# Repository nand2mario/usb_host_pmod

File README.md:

# USB Host PMOD

Design sources for a **dual-socket USB host PMOD** module, intended for interfacing USB devices on FPGA boards using [usb_hid_host](https://github.com/nand2mario/usb_hid_host). 

Included are [KiCAD sources](kicad/) and [production files](production/)(Gerber/BOM/PNP).

The easiest way to obtain the module is by following the [guide to directly order from JLCPCB](doc/guide.md).

This little design is done by [@regymm0](https://twitter.com/regymm0), [@ico_TC](https://twitter.com/ico_TC) and [@nand2mario](https://twitter.com/nand2mario).

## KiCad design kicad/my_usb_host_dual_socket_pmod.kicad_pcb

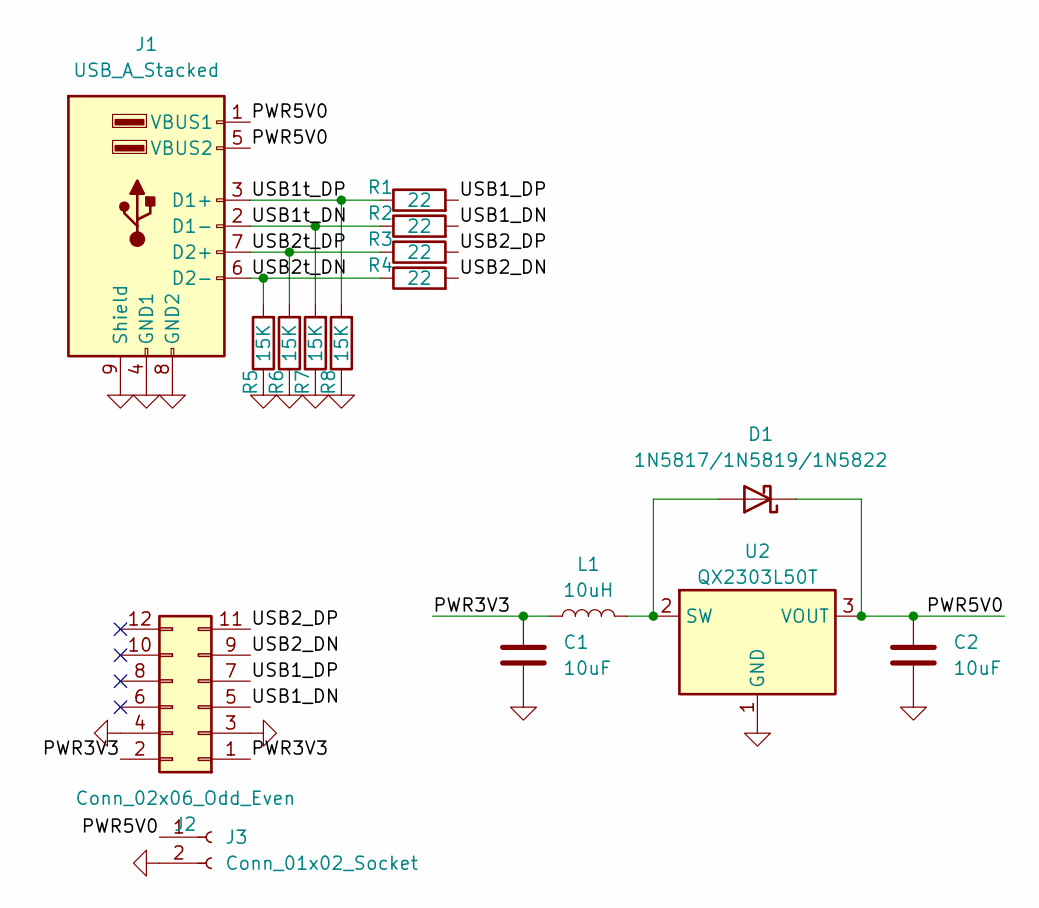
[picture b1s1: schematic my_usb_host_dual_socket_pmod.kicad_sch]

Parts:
C1, C2: 10uF; C_0402_1005Metric
D1: 1N5817/1N5819/1N5822; D_0402_1005Metric
J1: USB_A_Stacked; USB_A_Wuerth_61400826021_Horizontal_Stacked
J2: Conn_02x06_Odd_Even; PinHeader_2x06_P2.54mm_Horizontal
J3: Conn_01x02_Socket; PinSocket_1x02_P2.54mm_Vertical
L1: 10uH; L_0603_1608Metric
R1, R2, R3, R4: 22; R_0402_1005Metric
R5, R6, R7, R8: 15K; R_0402_1005Metric
U2: QX2303L50T; SOT-23

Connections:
/PWR3V3: C1.1, J2.1, J2.2, L1.1
/PWR5V0: C2.1, D1.1 (K), J1.1 (VBUS1), J1.5 (VBUS2), J3.1, U2.3 (VOUT)
/USB1_DN: J2.5, R2.2
/USB1_DP: J2.7, R1.2
/USB1t_DN: J1.2 (D1-), R2.1, R7.2
/USB1t_DP: J1.3 (D1+), R1.1, R8.2
/USB2_DN: J2.9, R4.2
/USB2_DP: J2.11, R3.2
/USB2t_DN: J1.6 (D2-), R4.1, R5.2
/USB2t_DP: J1.7 (D2+), R3.1, R6.2
GND: C1.2, C2.2, J1.4 (GND1), J1.8 (GND2), J1.9 (Shield), J2.3, J2.4, J3.2, R5.1, R6.1, R7.1, R8.1, U2.1 (GND)
unnamed: D1.2 (A), L1.2, U2.2 (SW)

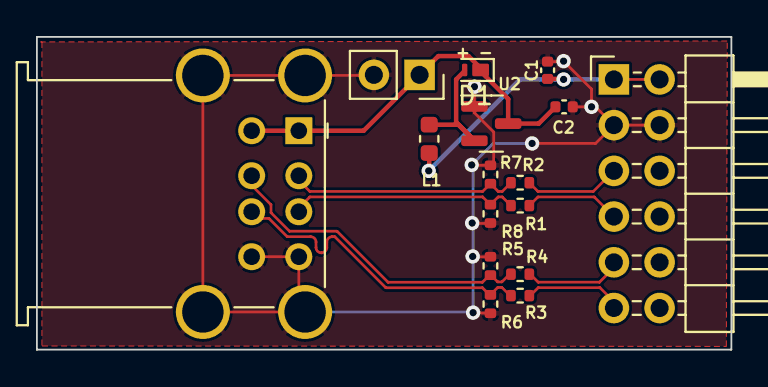
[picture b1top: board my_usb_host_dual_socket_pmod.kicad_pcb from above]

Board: 2 copper layers, 38.6 x 17.4 mm, 16 parts (0 on the bottom side), 12 nets.

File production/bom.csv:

Designator,Footprint,Quantity,Value,LCSC Part #
"C1, C2",0402,2,10uF,C15525
D1,0402,1,1N5817/1N5819/1N5822,C145508
J1,USB_A_Wuerth_61400826021_Horizontal_Stacked,1,USB_A_Stacked,C698206
J2,PinHeader_2x06_P2.54mm_Horizontal,1,Conn_02x06_Odd_Even,C492434
J3,PinSocket_1x02_P2.54mm_Vertical,1,Conn_01x02_Socket,NC
L1,0603,1,10uH,C1035
"R1, R2, R3, R4",0402,4,22,C25092
"R5, R6, R7, R8",0402,4,15K,C25756
U2,SOT-23,1,QX2303L50T,C219027

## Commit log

2023-10-20 README
2023-10-21 Create LICENSE
2024-01-18 fix 22 ohm resistor part number
2024-02-16 Replacement kicad_pcb supplied by Tavy
    Replaces D1 (0402 sized) with C907849 part (DSN-2 sized)
